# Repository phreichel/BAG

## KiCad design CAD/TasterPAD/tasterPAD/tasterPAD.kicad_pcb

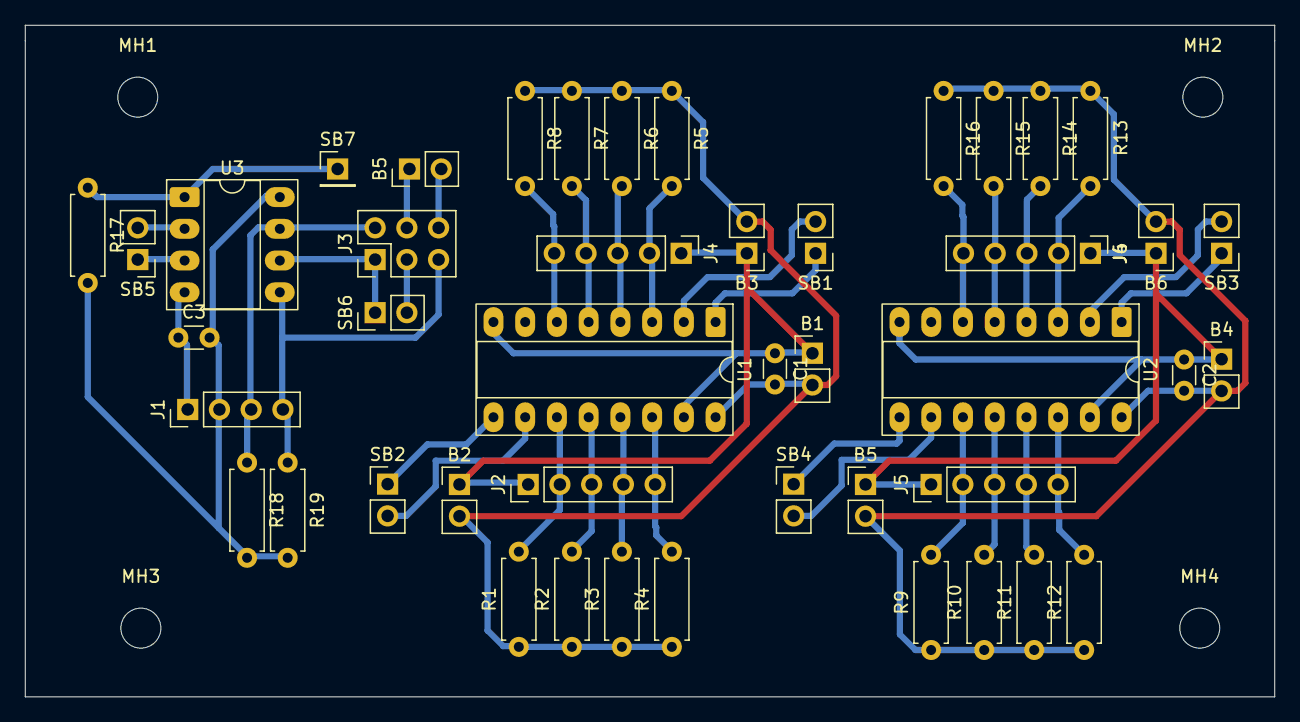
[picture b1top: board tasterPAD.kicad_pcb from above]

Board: 2 copper layers, 100.0 x 53.8 mm, 49 parts (0 on the bottom side), 25 nets.

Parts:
B1, B2, B3, B4, B5, B5#2, B6: PinHeader_1x02_P2.54mm_Vertical
C1, C2, C3: C; C_Disc_D3.0mm_W1.6mm_P2.50mm
J1: Conn_01x04_Pin; PinHeader_1x04_P2.54mm_Vertical
J2, J4, J5, J6: Conn_01x05_Pin; PinHeader_1x05_P2.54mm_Vertical
J3: SPI Programmer IF; PinHeader_2x03_P2.54mm_Vertical
MH1, MH2, MH3, MH4: MountingHole_3.2mm_M3
R1, R2, R3, R4, R5, R6, R7, R8, R9, R10, R11, R12, R13, R14, R15, R16, R17, R18, R19: 10k; R_Axial_DIN0207_L6.3mm_D2.5mm_P7.62mm_Horizontal
SB1, SB2, SB3, SB4, SB5, SB6: PinHeader_1x02_P2.54mm_Vertical
SB7: PinHeader_1x01_P2.54mm_Vertical
U1, U2: 74HC165; DIP-16_W7.62mm_Socket_LongPads
U3: ATtiny13A-P; DIP-8_W7.62mm_Socket_LongPads

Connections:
/CASCADE: SB2.2, SB4.1, U1.10 (DS), U2.9 (Q7)
/CLK: J3.1, SB1.2, SB3.2, SB6.1, U1.2 (CP), U2.2 (CP), U3.6 (PB1)
/IN01: J2.2, R1.2, U1.11 (D0)
/IN02: J2.3, R2.2, U1.12 (D1)
/IN03: J2.4, R3.2, U1.13 (D2)
/IN04: J2.5, R4.2, U1.14 (D3)
/IN05: J4.2, R5.2, U1.3 (D4)
/IN06: J4.3, R6.2, U1.4 (D5)
/IN07: J4.4, R7.2, U1.5 (D6)
/IN08: J4.5, R8.2, U1.6 (D7)
/IN09: J5.2, R9.2, U2.11 (D0)
/IN10: J5.3, R10.2, U2.12 (D1)
/IN11: J5.4, R11.2, U2.13 (D2)
/IN12: J5.5, R12.2, U2.14 (D3)
/IN13: J6.2, R13.2, U2.3 (D4)
/IN14: J6.3, R14.2, U2.4 (D5)
/IN15: J6.4, R15.2, U2.5 (D6)
/IN16: J6.5, R16.2, U2.6 (D7)
/PL: SB1.1, SB3.1, SB5.1, U1.1 (~PL), U2.1 (~PL), U3.3 (PB4)
/Q7: SB2.1, SB5.2, U1.9 (Q7), U3.2 (PB3)
/RESET: J3.3, R17.1, SB6.2, SB7.1, U3.1 (~RESET/PB5)
/SCL: J1.4, J3.5, R19.1, U3.5 (PB0)
/SDA: J1.3, J3.2, R18.1, U3.7 (PB2)
GND: B1.1, B2.1, B3.1, B4.1, B5.1, B5#2.1, B6.1, C1.1, C2.1, C3.1, J1.1, J2.1, J3.4, J4.1, J5.1, J6.1, SB4.2, U1.8 (GND), U1.15 (~CE), U2.8 (GND), U2.10 (DS), U2.15 (~CE), U3.4 (GND)
VCC: B1.2, B2.2, B3.2, B4.2, B5.2, B5#2.2, B6.2, C1.2, C2.2, C3.2, J1.2, J3.6, R1.1, R2.1, R3.1, R4.1, R5.1, R6.1, R7.1, R8.1, R9.1, R10.1, R11.1, R12.1, R13.1, R14.1, R15.1, R16.1, R17.2, R18.2, R19.2, U1.16 (VCC), U2.16 (VCC), U3.8 (VCC)

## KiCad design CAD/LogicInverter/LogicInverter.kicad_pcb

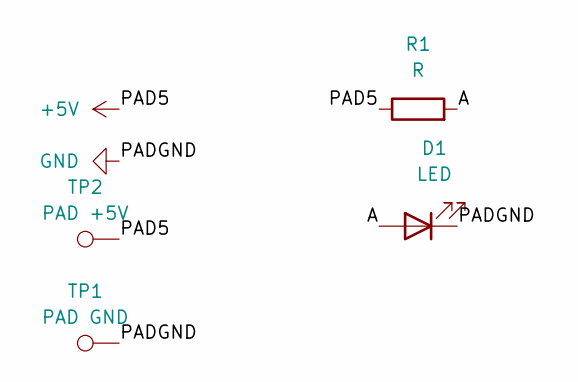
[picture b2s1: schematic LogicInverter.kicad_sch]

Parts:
D1: LED; LED_D4.0mm
R1: R; R_Axial_DIN0207_L6.3mm_D2.5mm_P7.62mm_Horizontal
TP1: PAD GND; TestPoint_Pad_D4.0mm
TP2: PAD +5V; TestPoint_Pad_D4.0mm

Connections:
+5V: R1.1, TP2.1
/A: D1.2 (A), R1.2
GND: D1.1 (K), TP1.1

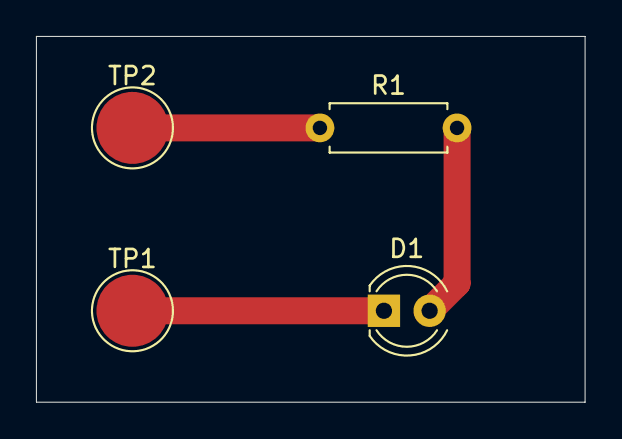
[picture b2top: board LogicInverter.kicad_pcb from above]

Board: 2 copper layers, 30.5 x 20.3 mm, 4 parts (0 on the bottom side), 3 nets.

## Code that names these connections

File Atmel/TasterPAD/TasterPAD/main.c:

#ifndef F_CPU
#define F_CPU 1200000UL   // ATtiny13A CKDIV8
#endif

#include <stdint.h>
#include <avr/io.h>
#include <util/delay.h>

/* =======================
 *  SHIFT REGISTER INPUT
 * ======================= */
#define PIN_DATA   PB3   // Q7
#define PIN_PL     PB4   // Parallel Load (LOW)
#define PIN_CLK    PB1   // Shift Clock
#define DEBOUNCE_MS 10

/* =======================
 *  "SLOW I2C-LIKE" BUS CONFIG (Open-Drain)
 * ======================= */
#define I2C_SCL    PB0
#define I2C_SDA    PB2
#define I2C_ADDR   0x42

/* =======================
 *  TIMING (ms, absichtlich LANG)
 *  -> damit ESP32 alles locker dekodieren kann
 * ======================= */
#define BUS_IDLE_MS        5    // Bus muss vor START stabil HIGH/HIGH sein
#define START_HOLD_MS      3    // SDA LOW bei SCL HIGH (START) halten
#define STOP_HOLD_MS       3    // SDA HIGH bei SCL HIGH (STOP) halten

#define BIT_SETUP_MS       1    // DATA stabilisieren bevor SCL HIGH
#define SCL_HIGH_MS        2
#define SCL_LOW_MS         2

#define BYTE_GAP_MS        2    // Pause zwischen Bytes (zusätzlich zum SCL low)
#define ACK_SLOT_MS        2    // "ACK-Clock" High-Zeit (Dummy, keine Auswertung)

#define FRAME_GAP_MS      20    // nach STOP: eindeutige Frame-Trennung

#define DEBUG_PERIOD_MS  500    // periodisches Senden (Debug)

/* =======================
 *  Open-Drain Primitives
 * ======================= */
static inline void sda_low(void) {
    DDRB |=  (1 << I2C_SDA);
    PORTB &= ~(1 << I2C_SDA);
}
static inline void sda_release(void) {
    DDRB &= ~(1 << I2C_SDA);   // extern Pull-Up => HIGH
}

static inline void scl_low(void) {
    DDRB |=  (1 << I2C_SCL);
    PORTB &= ~(1 << I2C_SCL);
}
static inline void scl_release(void) {
    DDRB &= ~(1 << I2C_SCL);   // extern Pull-Up => HIGH
}

/* =======================
 *  Robust "I2C-like" signaling
 * ======================= */
static inline void bus_idle(void)
{
    sda_release();
    scl_release();
    _delay_ms(BUS_IDLE_MS);
}

static inline void i2c_like_start(void)
{
    bus_idle();

    // START: SDA fällt bei SCL HIGH
    sda_low();
    _delay_ms(START_HOLD_MS);

    // danach SCL LOW (Frame läuft)
    scl_low();
    _delay_ms(SCL_LOW_MS);
}

static inline void i2c_like_stop(void)
{
    // Vorbereitung: SDA LOW, SCL LOW
    sda_low();
    scl_low();
    _delay_ms(SCL_LOW_MS);

    // SCL HIGH
    scl_release();
    _delay_ms(SCL_HIGH_MS);

    // STOP: SDA steigt bei SCL HIGH
    sda_release();
    _delay_ms(STOP_HOLD_MS);
}

static inline void i2c_like_clock_bit(void)
{
    // SCL HIGH -> sample point
    scl_release();
    _delay_ms(SCL_HIGH_MS);

    // SCL LOW
    scl_low();
    _delay_ms(SCL_LOW_MS);
}

static inline void i2c_like_write_byte(uint8_t byte)
{
    for (uint8_t i = 0; i < 8; i++)
    {
        // DATA setzen (MSB first)
        if (byte & 0x80) sda_release();
        else             sda_low();

        _delay_ms(BIT_SETUP_MS);

        i2c_like_clock_bit();

        byte <<= 1;
    }

    // ACK-SLOT: Dummy-Clock, DATA loslassen, aber NICHT auswerten
    sda_release();
    _delay_ms(BIT_SETUP_MS);

    // ein separater "ACK clock"
    scl_release();
    _delay_ms(ACK_SLOT_MS);
    scl_low();
    _delay_ms(SCL_LOW_MS);

    // Gap zwischen Bytes für Decoder-Resync
    _delay_ms(BYTE_GAP_MS);
}

/* =======================
 *  SHIFT REGISTER READ
 * ======================= */
static inline void clk_pulse(void)
{
    PORTB |=  (1 << PIN_CLK);
    _delay_us(5);
    PORTB &= ~(1 << PIN_CLK);
    _delay_us(5);
}

uint16_t read_shift_register(void)
{
    uint16_t value = 0;

    // Parallel Load
    PORTB &= ~(1 << PIN_PL);
    _delay_us(20);
    PORTB |=  (1 << PIN_PL);
    _delay_us(20);

    PORTB &= ~(1 << PIN_CLK);

    for (uint8_t i = 0; i < 16; i++)
    {
        value <<= 1;
        if (PINB & (1 << PIN_DATA))
            value |= 1;
        clk_pulse();
    }

    return value;
}

uint16_t debounce_read(void)
{
    uint16_t prev = read_shift_register();

    for (;;)
    {
        _delay_ms(DEBOUNCE_MS);
        uint16_t curr = read_shift_register();
        if (curr == prev)
            return curr;
        prev = curr;
    }
}

/* =======================
 *  EVENT SEND (I2C-like)
 *  Packet: Status(16) + Diff(16) => 4 bytes MSB first
 * ======================= */
void output_event_i2c_like(uint16_t curr_state)
{
    static uint16_t prev_state = 0xFFFF;

    uint16_t diff = curr_state ^ prev_state;

    uint32_t packet =
        ((uint32_t)curr_state << 16) |
        (uint32_t)diff;

    // "Frame"
    i2c_like_start();

    // Address + W (wie I2C: 7bit<<1)
    i2c_like_write_byte((uint8_t)(I2C_ADDR << 1));

    // 4 Datenbytes MSB first
    for (int8_t i = 3; i >= 0; i--)
        i2c_like_write_byte((uint8_t)((packet >> (8 * i)) & 0xFF));

    i2c_like_stop();

    // harte Frame-Trennung
    _delay_ms(FRAME_GAP_MS);

    prev_state = curr_state;
}

/* =======================
 *  MAIN
 * ======================= */
int main(void)
{
    // Shift-Register IO
    DDRB &= ~(1 << PIN_DATA);
    DDRB |=  (1 << PIN_PL) | (1 << PIN_CLK);

    PORTB |=  (1 << PIN_DATA); // Pull-Up
    PORTB |=  (1 << PIN_PL);
    PORTB &= ~(1 << PIN_CLK);

    // Bus idle
    sda_release();
    scl_release();

    for (;;)
    {
        uint16_t stable = debounce_read();
        output_event_i2c_like(stable);

        // Debug: periodisch senden, egal ob Änderung
        _delay_ms(DEBUG_PERIOD_MS);
    }
}

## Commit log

2024-11-04 Inital collection of already previous developed programms
2024-11-05 add Electric Folder for KiCAD
2024-11-19 Introduce QTree
2025-01-08 New Schema for Four Cable
2025-03-11 adsf
2025-03-11 test
2025-03-12 New Ivy Settings and cleanup
2025-03-12 J3D: Clean Errors and Warnings
2025-03-12 Set up Ivy for local projects
2025-03-12 add ivy util
2025-03-12 Added Start of Particles
2025-03-13 added JADE
2025-03-13 Added Scripts
2025-03-29 Added Open SCAD Files to the bag.
2025-04-02 Updating 3D Constructions
2025-04-03 Added Sinoid like Gear Example
2025-04-06 Removing unfinished Particle System
2025-04-14 Zwischenkommit
2025-04-14 anges
2025-04-14 Update time list
2025-04-14 task Tracker Repariert und Datenformat angepasst
2025-04-14 Task Tracker Fix: mehrfache zeilen vermeiden
2025-04-14 Excel excample
2025-04-15 Synch Tasks
2025-04-15 Tasks
2025-04-17 Tasks update
2025-04-17 Tasks, CAD für Rover, Rover Code changes
2025-04-17 taskStatus und RoverBaseplate
2025-06-27 cleanup work computer
2025-06-28 Add random projects
2025-06-28 Adding projects
2025-07-01 New Projects
2025-07-01 Restructure
2025-07-03 Removing Unnecessary Projects
2025-07-09 New CORE Project
2025-07-09 attempts to switch to different GL model
2025-07-10 Extending the CORE!
2025-07-11 New core features
2025-07-13 CORE Gui System primer
2025-07-13 Rail and Sled CAD
2025-07-14 Changes in CORE Layouting
2025-07-17 New SCAD Designs: Rail And Sled, Capstan
2025-07-17 CORE GUI Layout and Layer Component updates
2025-07-19 Added a Label
2025-07-19 GUI Code simplification
2025-07-20 GUI Theme and Style implementation
2025-07-21 Input Redesign
2025-07-22 Starting Virtual System
2025-07-25 Updated Virtiual Axes
2025-07-26 Virtual Mapping Semi Complete
2025-08-04 wristadapter and robarm
2025-08-08 Serial Test
2025-08-12 Updates: actuators.scad, ROBARM-V01
2025-08-20 New CAD
2025-08-23 New Better Steel Cube Corner Piece - INVDB beginnigs
2025-09-04 Capstan Stuff
2025-09-06 some java stuff
2025-09-17 CAD, CODE, READING for Cable Bot
2025-09-21 Cable Robot Updates - Short before Calibration Programming
2025-09-28 Cable Mover V02 Source Code extensions
2025-10-18 Cable 3 Intermediate
2025-10-18 CABLE 3 - Intermediate
2025-10-18 fix names
2025-10-18 sdfs
2025-10-19 Cable V3 - Functional Serial Remote. But Buggy Movement.
2025-10-19 Cable 03 some fixes
2025-10-21 Reorganization
2025-10-22 Adding Oscillator KiCAD
2025-10-26 There you are
2025-10-27 Add MIT License to the project
2025-10-29 Arbeitsbuecher
2025-10-29 synch
2025-11-02 fix some java things
2025-11-03 change to local mosquitto instance
2025-11-04 Word Doc Starts
2025-11-19 logic inverter KiCAD
2025-11-19 Opferplatte fuer cnc
2025-11-19 CNC Update
2025-11-19 upgerad
2025-11-30 Mostly taster PCB Design
2025-11-30 LogicInverter
2025-12-01 cleanup
2025-12-01 Full routed PCB - V1
2025-12-02 updated Taster PCB
2025-12-02 Final PcB
2025-12-02 Gerber Files Added
2025-12-02 Generated GCode Files
2025-12-02 added modifictaion for cnc
2025-12-06 new homesassist
2025-12-06 ignore 'alexa' wav files
2025-12-07 add linux shutdown
2025-12-07 fix error bug
2025-12-08 Added TasterPAD code project
2025-12-16 TasterPAD abschluss
2025-12-21 Cable_Mover Doku
2025-12-22 Relocation of Resources
2025-12-23 linux porting
2026-01-01 linux speech script and first os loaders
2026-01-07 vbr and dice
2026-01-10 POS System Loader
2026-01-11 sync
2026-01-11 Remove Garbage
2026-01-11 new cli if
2026-01-19 things
2026-01-25 Added: FreeCAD Fishbone Gear
2026-01-25 some changes
2026-01-25 another gear
2026-01-25 gear completion
2026-02-16 several projects
2026-02-16 some cpp
2026-03-04 stuff
2026-03-15 Added QR Generator
2026-04-01 Two New Java Projects
2026-04-04 JDoc App
2026-05-23 New Stuff
2026-05-24 Bessere Sprachauswahl
2026-05-27 Added Companion
2026-05-27 Animated Companion
2026-06-14 Transfer
2026-06-14 Transfer of HomeInv App
